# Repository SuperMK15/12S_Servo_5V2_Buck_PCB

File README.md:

# 12S to Servo 5V2 Buck PCB

Custom Battery Eliminator Circuit (BEC) PCB built around the **LM65680RZYR** buck switching regulator IC, efficiently stepping down a 12S battery input (36V–50.4V) to 5.2V and supporting up to 8A of continuous draw for VTOL drone servo rails.

## Features

* Built around the LM65680RZYR buck switching regulator IC.
* 12S battery input supporting 36V to 50.4V via an XT30 male connector.
* 5.2V output supporting up to 8A maximum draw via an XT30 female connector.
* Input overvoltage protection utilizing an SMCJ54A TVS diode.
* Dedicated test point for Power Good (PG) monitoring.
* Two mounting holes, following a standard 30.5 × 30.5 mm M3 mounting pattern.

## PCB Layers

### Front Copper (Layer 1)

### Ground (Layer 2)

### Ground (Layer 3)

### Back Copper (Layer 4)

## Design Files

Designed in **KiCad 10**. Includes the complete schematic, PCB layout, custom footprints/symbols, and manufacturing files.

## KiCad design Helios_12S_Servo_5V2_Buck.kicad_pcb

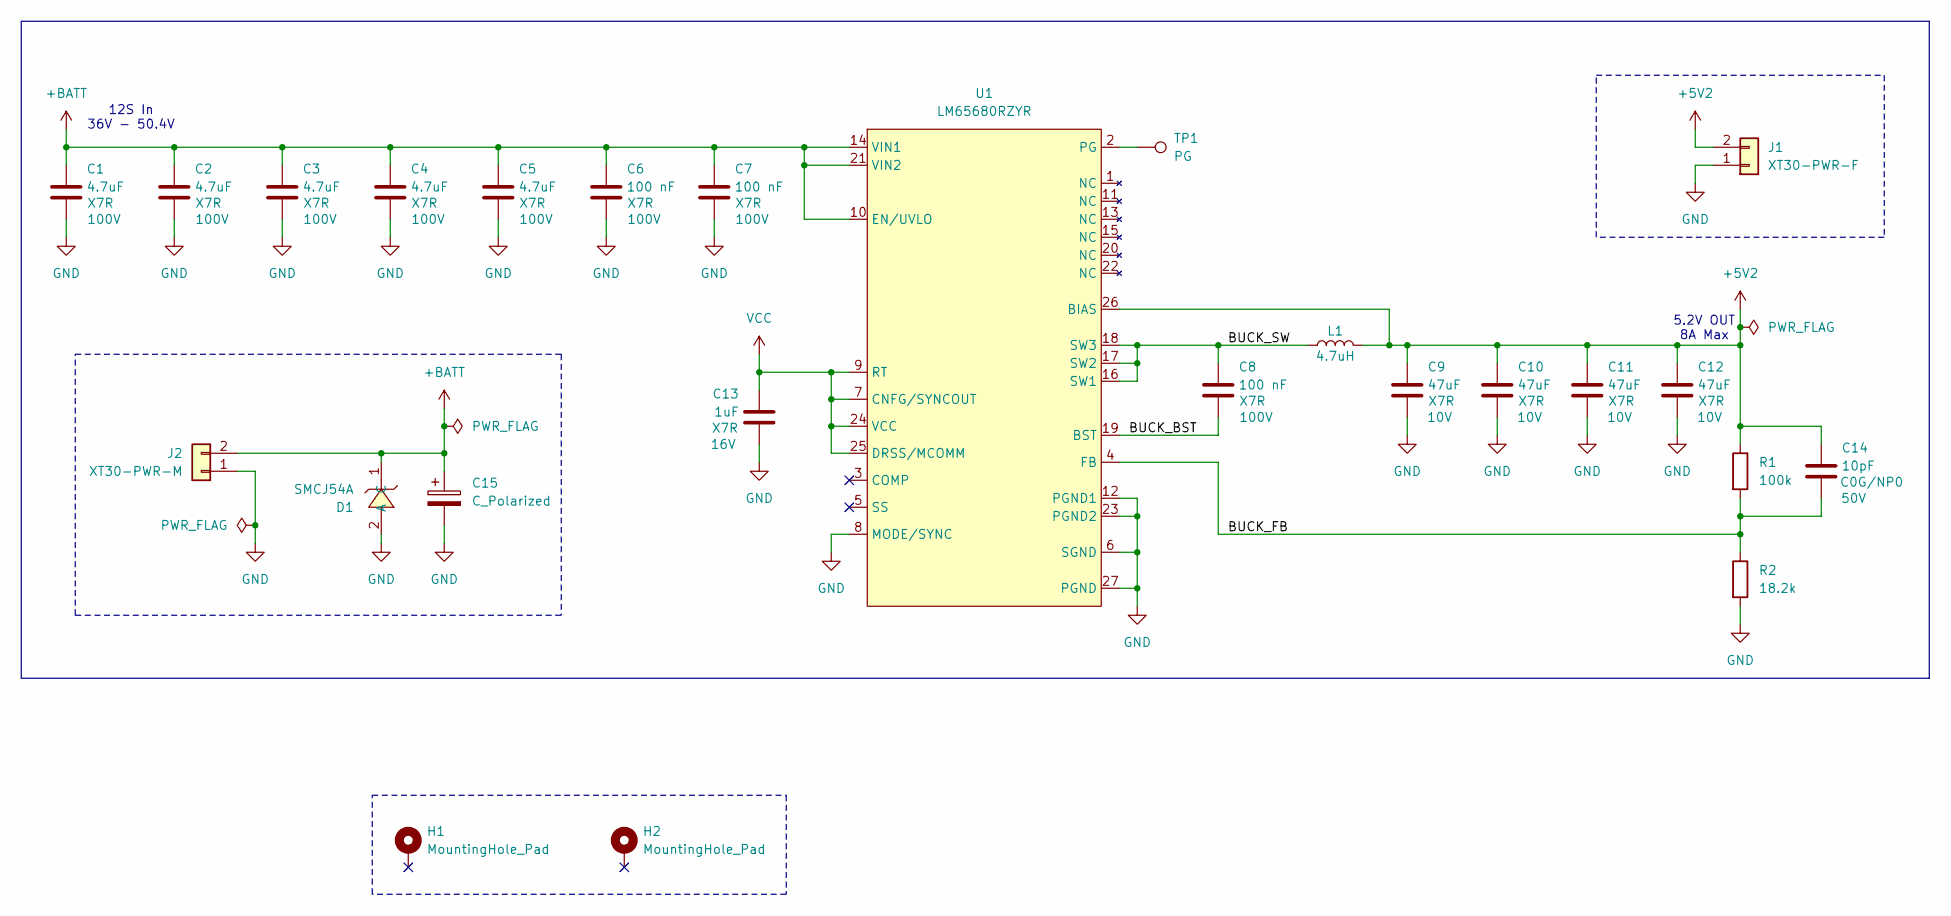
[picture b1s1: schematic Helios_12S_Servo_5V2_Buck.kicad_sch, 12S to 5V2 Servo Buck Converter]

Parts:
C1, C2, C3, C4, C5: 4.7uF; C_1210_3225Metric; Temp Rating X7R; LCSC C22877898
C6, C7, C8: 100 nF; C_0603_1608Metric; Temp Rating X7R; LCSC C15725
C9, C10, C11, C12: 47uF; C_1210_3225Metric; Temp Rating X7R; LCSC C84494
C13: 1uF; C_0402_1005Metric; Temp Rating X7R; LCSC C49210445
C14: 10pF; C_0402_1005Metric; Temp Rating C0G/NP0; LCSC C32949
C15: C_Polarized; CAP-SMD_BD8.0-L8.3-W8.3-FD; LCSC C401897
D1: SMCJ54A; SMC_L6.9-W5.9-LS7.9-RD; LCSC C720068
H1, H2: MountingHole_Pad; MountingHole_3.2mm_M3_DIN965_Pad
J1: XT30-PWR-F; AMASS_XT30PW-F_1x02_P2.50mm_Horizontal; LCSC C2913282
J2: XT30-PWR-M; AMASS_XT30PW-M_1x02_P2.50mm_Horizontal; LCSC C431092
L1: 4.7uH; IND-SMD_L9.8-W8.8_SRYH.0885.YF; LCSC C50325381
R1: 100k; R_0402_1005Metric; LCSC C25741
R2: 18.2k; R_0402_1005Metric; LCSC C2076827
TP1: PG; TestPoint_Pad_D1.0mm
U1: LM65680RZYR; VQFN-26_L4.5-W4.5-LM65660-Q1; LCSC C53201929

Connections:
+5V2: C9.1, C10.1, C11.1, C12.1, C14.1, J1.2, L1.2, R1.1, U1.26 (BIAS)
+BATT: C1.1, C2.1, C3.1, C4.1, C5.1, C6.1, C7.1, C15.1, D1.1 (C), J2.2, U1.10 (EN/UVLO), U1.14 (VIN1), U1.21 (VIN2)
/BUCK_BST: C8.2, U1.19 (BST)
/BUCK_FB: C14.2, R1.2, R2.1, U1.4 (FB)
/BUCK_SW: C8.1, L1.1, U1.16 (SW1), U1.17 (SW2), U1.18 (SW3)
GND: C1.2, C2.2, C3.2, C4.2, C5.2, C6.2, C7.2, C9.2, C10.2, C11.2, C12.2, C13.2, C15.2, D1.2 (A), J1.1, J2.1, R2.2, U1.6 (SGND), U1.8 (MODE/SYNC), U1.12 (PGND1), U1.23 (PGND2), U1.27 (PGND)
unnamed: TP1.1 (1_1), U1.2 (PG)
VCC: C13.1, U1.7 (CNFG/SYNCOUT), U1.9 (RT), U1.24 (VCC), U1.25 (DRSS/MCOMM)

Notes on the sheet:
5.2V OUT 8A Max
12S In 36V - 50.4V

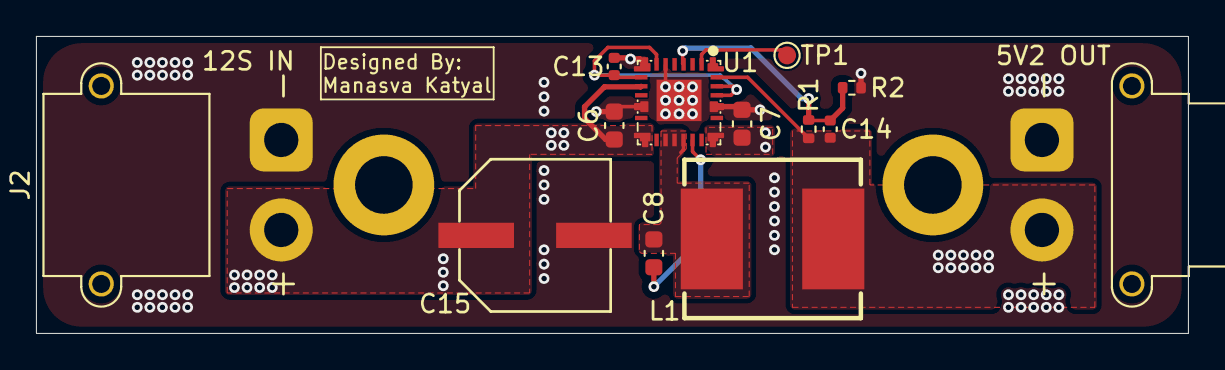
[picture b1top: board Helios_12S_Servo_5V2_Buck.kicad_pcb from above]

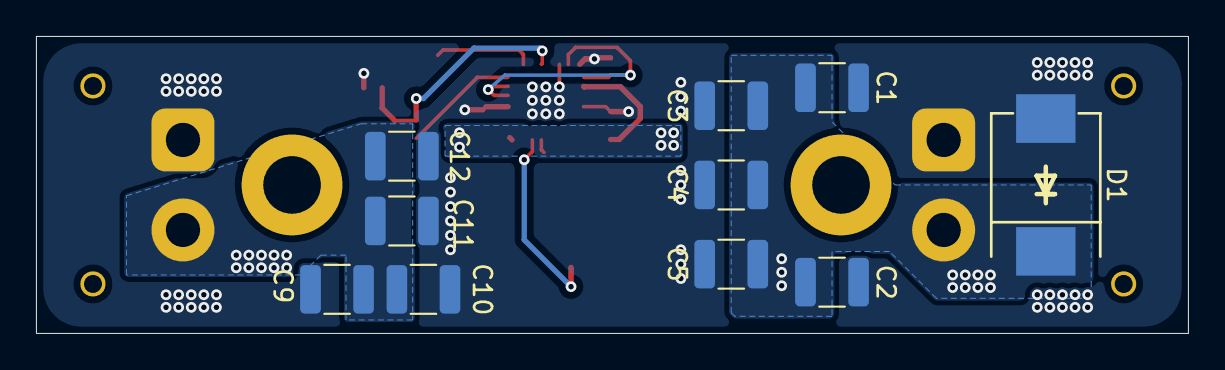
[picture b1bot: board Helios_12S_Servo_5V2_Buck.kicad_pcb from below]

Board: 4 copper layers, 64.0 x 16.5 mm, 25 parts (10 on the bottom side), 8 nets.
